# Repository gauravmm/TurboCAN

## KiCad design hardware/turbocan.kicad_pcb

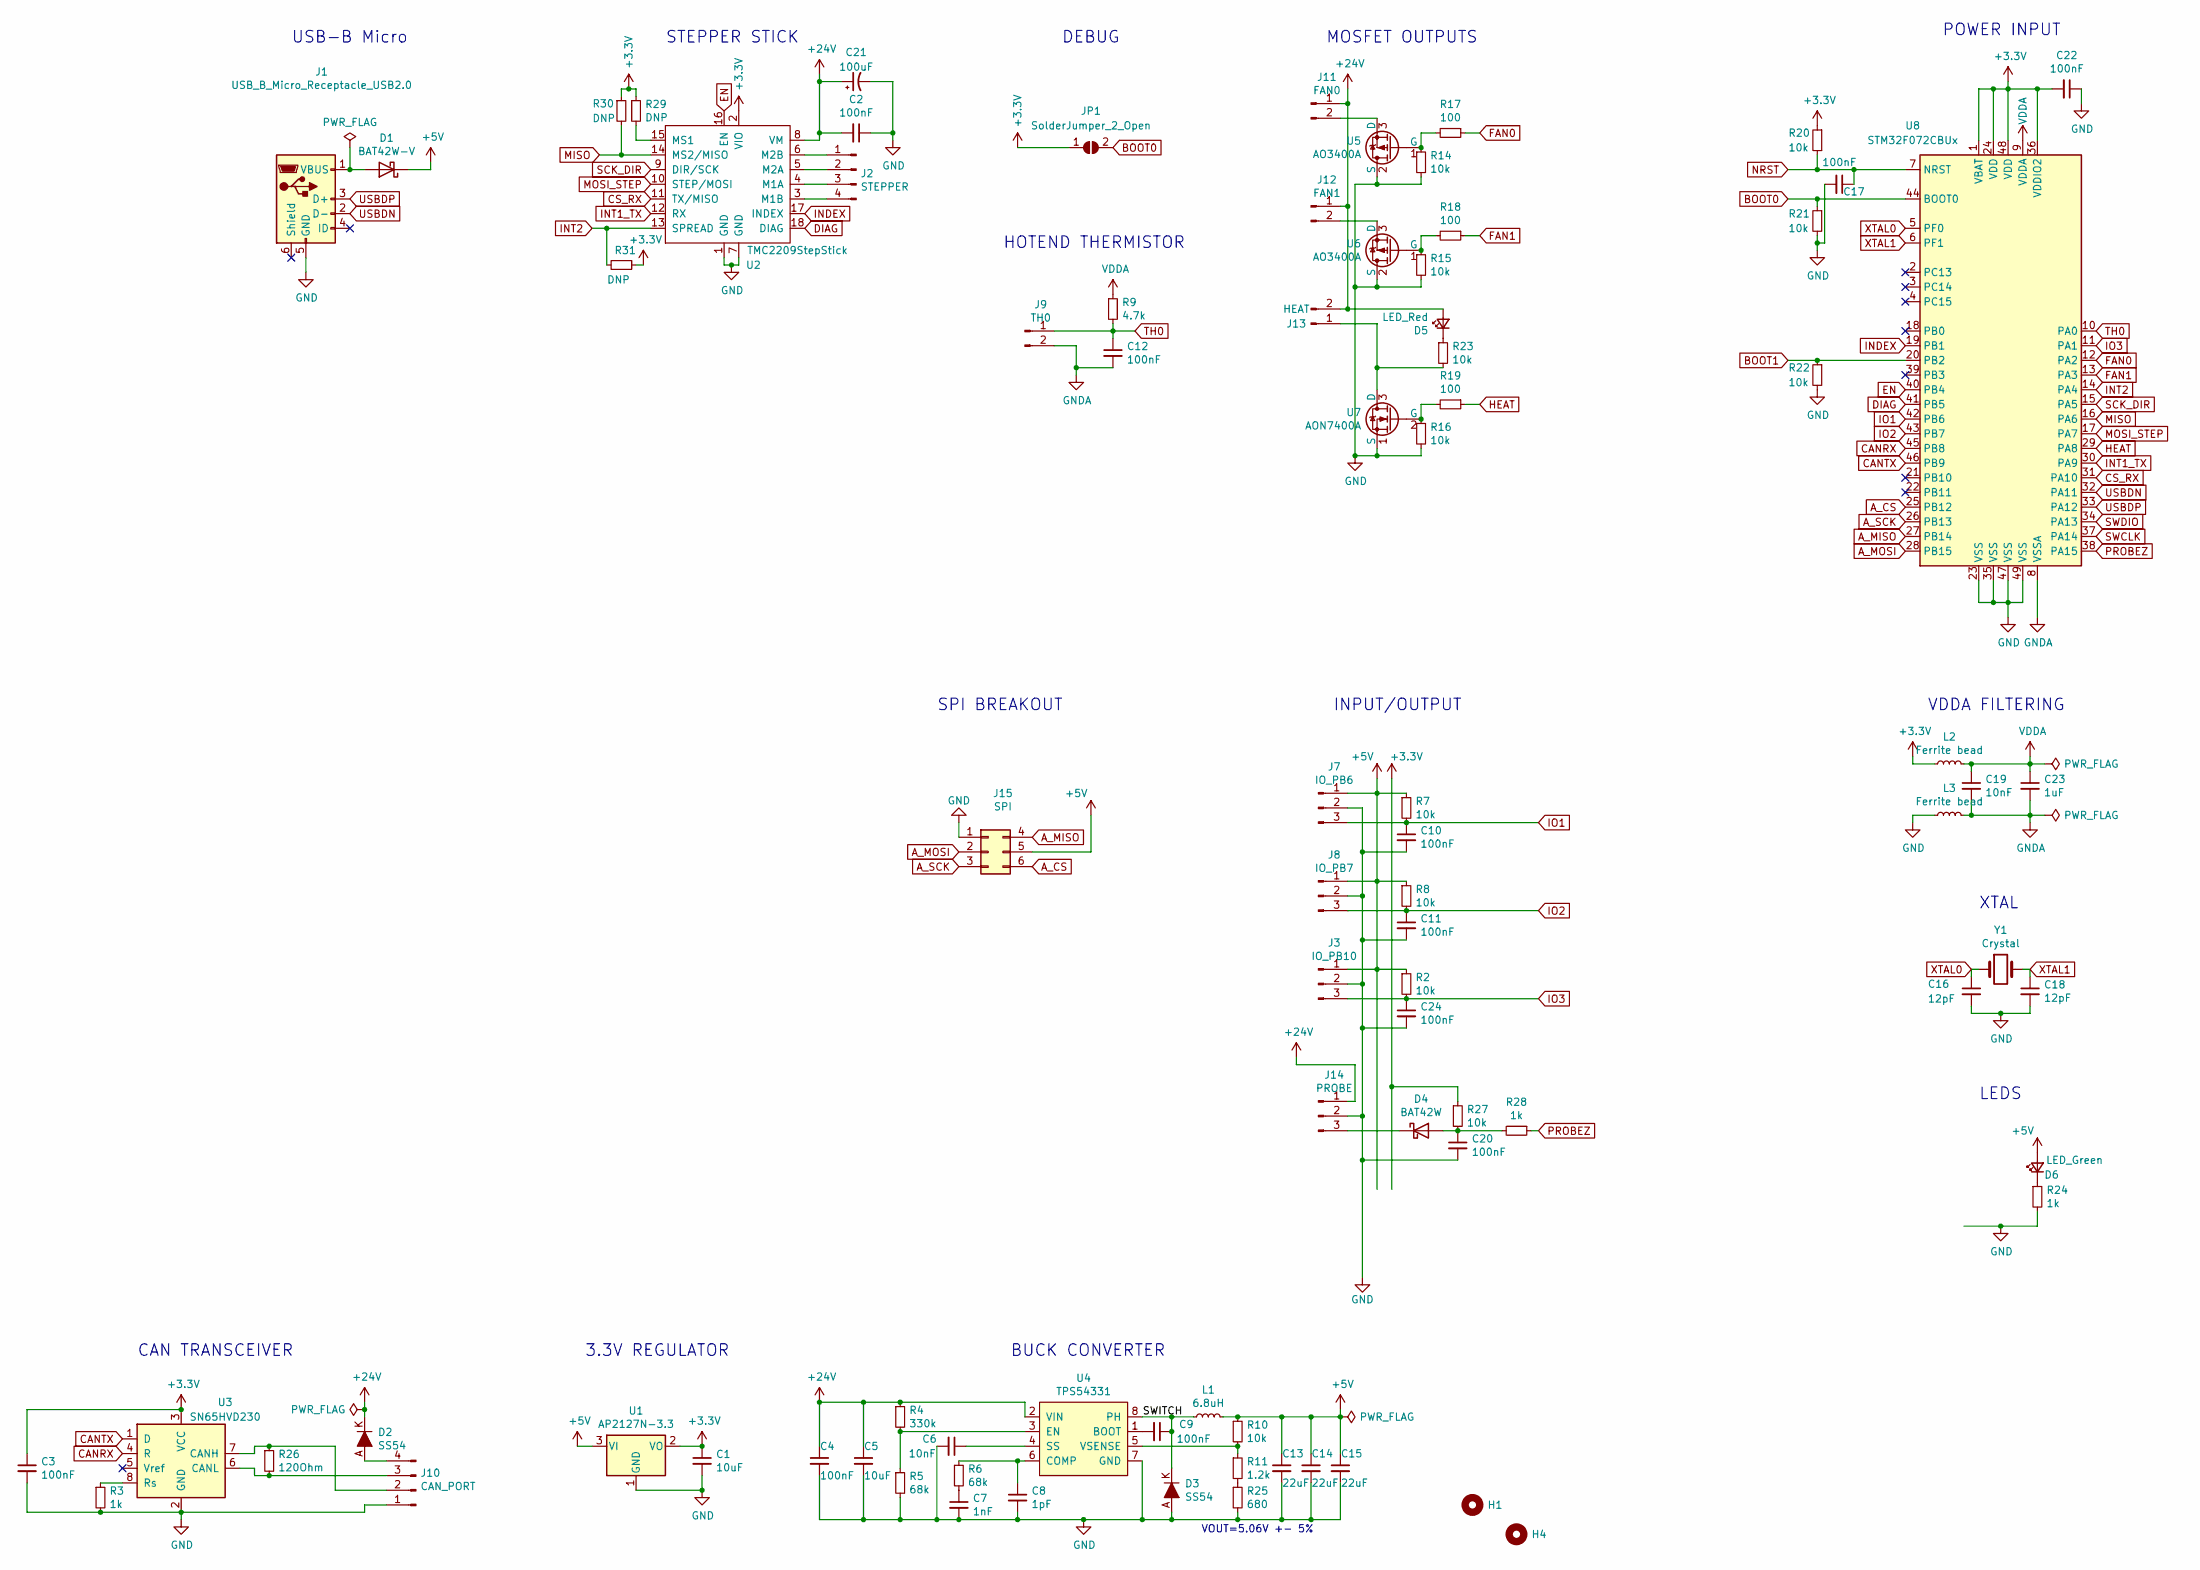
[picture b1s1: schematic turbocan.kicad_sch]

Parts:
C1, C5: 10uF; C_0805_2012Metric; LCSC Part Number C15850
C2, C3, C4, C9, C10, C11, C12, C17, C20, C22, C24: 100nF; C_0402_1005Metric; LCSC Part Number C1525
C6, C19: 10nF; C_0402_1005Metric; LCSC Part Number C15195
C7: 1nF; C_0402_1005Metric; LCSC Part Number C1523
C8: 1pF; C_0402_1005Metric; LCSC Part Number C1550
C13, C14, C15: 22uF; C_0805_2012Metric; LCSC Part Number C45783
C16, C18: 12pF; C_0402_1005Metric; LCSC Part Number C1547
C21: 100uF; CP_Elec_8x10; LCSC Part Number C59944
C23: 1uF; C_0402_1005Metric; LCSC Part Number C52923
D1: BAT42W-V; D_SOD-123; LCSC Part Number C8598
D2, D3: SS54; DO-214AC; MPN SS14; Digi-Key_PN SS14CT-ND
D4: BAT42W; D_SOD-123; LCSC Part Number C8598
D5: LED_Red; LED_0603_1608Metric; LCSC Part Number C2286
D6: LED_Green; LED_0603_1608Metric; LCSC Part Number C72043
H1, H4: MountingHole; MountingHole_3.2mm_M3_DIN965_Pad
J1: USB_B_Micro_Receptacle_USB2.0; USB_Micro-B_Amphenol_10118194_Horizontal
J2: STEPPER; JST_XH_B4B-XH-A_1x04_P2.50mm_Vertical
J3: IO_PB10; JST_XH_B3B-XH-A_1x03_P2.50mm_Vertical
J7: IO_PB6; JST_XH_B3B-XH-A_1x03_P2.50mm_Vertical
J8: IO_PB7; JST_XH_B3B-XH-A_1x03_P2.50mm_Vertical
J9: TH0; JST_XH_B2B-XH-A_1x02_P2.50mm_Vertical
J10: CAN_PORT; JST_XH_B4B-XH-A_1x04_P2.50mm_Vertical
J11: FAN0; JST_XH_B2B-XH-A_1x02_P2.50mm_Vertical
J12: FAN1; JST_XH_B2B-XH-A_1x02_P2.50mm_Vertical
J13: HEAT; JST_XH_B2B-XH-A_1x02_P2.50mm_Vertical
J14: PROBE; JST_XH_B3B-XH-A_1x03_P2.50mm_Vertical
J15: SPI; PinHeader_2x03_P2.54mm_Vertical
JP1: SolderJumper_2_Open; SolderJumper-2_P1.3mm_Open_TrianglePad1.0x1.5mm
L1: 6.8uH; L_SMD_7.3x6.8; LCSC Part Number C207841
L2: Ferrite bead; L_0805_2012Metric; LCSC Part Number C1017
L3: Ferrite bead; L_0805_2012Metric
R2, R7, R8, R10, R14, R15, R16, R20, R21, R22, R27: 10k; R_0402_1005Metric; LCSC Part Number C25744
R3, R24, R28: 1k; R_0402_1005Metric; LCSC Part Number C11702
R4: 330k; R_0402_1005Metric; LCSC Part Number C25778
R5, R6: 68k; R_0402_1005Metric; LCSC Part Number C36871
R9: 4.7k; R_0805_2012Metric; LCSC Part Number C17673
R11: 1.2k; R_0402_1005Metric; LCSC Part Number C25862
R17, R18, R19: 100; R_0402_1005Metric; LCSC Part Number C25076
R23: 10k; R_0402_1005Metric; LCSC Part Number C11702
R25: 680; R_0402_1005Metric; LCSC Part Number C25130
R26: 120Ohm; R_0805_2012Metric; LCSC Part Number C17437
R29, R30, R31: DNP; R_0402_1005Metric
U1: AP2127N-3.3; SOT-23; LCSC Part Number C5446
U2: TMC2209StepStick
U3: SN65HVD230; SOIC-8_3.9x4.9mm_P1.27mm; LCSC Part Number C12084
U4: TPS54331; SOIC-8_3.9x4.9mm_P1.27mm; LCSC Part Number C9865
U5, U6: AO3400A; SOT-23; LCSC Part Number C344010
U7: AON7400A; DFN-8-1EP_3x3mm_P0.65mm_EP1.7x2.05mm_Thermal_Pad; LCSC C85734
U8: STM32F072CBUx; QFN-48-1EP_7x7mm_P0.5mm_EP5.6x5.6mm; LCSC Part Number C92504
Y1: Crystal; Crystal_SMD_5032-2Pin_5.0x3.2mm; LCSC Part Number C115962

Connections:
+3V3: C1.1, C3.1, C22.2, JP1.1 (A), L2.1, R20.1, R27.1, R29.1, R30.1, R31.1, U1.2 (VO), U2.2 (VIO), U3.3 (VCC), U8.1 (VBAT), U8.24 (VDD), U8.36 (VDDIO2), U8.48 (VDD)
+5V: C13.1, C14.1, C15.1, D1.1 (K), D6.2 (A), J3.1, J7.1, J8.1, J15.5, L1.2, R2.1, R7.1, R8.1, R10.1, U1.3 (VI)
+24V: C2.2, C4.1, C5.1, C21.1, D2.K, D5.2 (A), J11.1, J12.1, J13.2, J14.1, R4.1, U2.8 (VM), U4.2 (VIN)
/SWITCH: C9.1, D3.K, L1.1, U4.8 (PH)
A_CS: J15.6, U8.25 (PB12)
A_MISO: J15.4, U8.27 (PB14)
A_MOSI: J15.2, U8.28 (PB15)
A_SCK: J15.3, U8.26 (PB13)
BOOT0: JP1.2 (B), R21.1, U8.44 (BOOT0)
BOOT1: R22.1, U8.20 (PB2)
CANRX: U3.4 (R), U8.45 (PB8)
CANTX: U3.1 (D), U8.46 (PB9)
CS_RX: U2.11 (TX/MISO), U8.31 (PA10)
DIAG: U2.18 (DIAG), U8.41 (PB5)
EN: U2.16 (EN), U8.40 (PB4)
FAN0: R17.1, U8.12 (PA2)
FAN1: R18.1, U8.13 (PA3)
GND: C1.2, C2.1, C3.2, C4.2, C5.2, C6.2, C7.2, C8.2, C10.2, C11.2, C13.2, C14.2, C15.2, C16.2, C17.2, C18.2, C20.2, C21.2, C22.1, C24.2, D3.A, J1.5 (GND), J3.2, J7.2, J8.2, J10.1, J14.2, J15.1, L3.1, R3.2, R5.2, R14.2, R15.2, R16.2, R21.2, R22.2, R24.2, R25.2, U1.1 (GND), U2.1 (GND), U2.7 (GND), U3.2 (GND), U4.7 (GND), U5.2 (S), U6.2 (S), U7.1 (S), U8.23 (VSS), U8.35 (VSS), U8.47 (VSS), U8.49 (VSS)
GNDA: C12.2, C19.2, C23.2, J9.2, L3.2, U8.8 (VSSA)
HEAT: R19.1, U8.29 (PA8)
INDEX: U2.17 (INDEX), U8.19 (PB1)
INT1_TX: U2.12 (RX), U8.30 (PA9)
INT2: R31.2, U2.13 (SPREAD), U8.14 (PA4)
IO1: C10.1, J7.3, R7.2, U8.42 (PB6)
IO2: C11.1, J8.3, R8.2, U8.43 (PB7)
IO3: C24.1, J3.3, R2.2, U8.11 (PA1)
MISO: R30.2, U2.14 (MS2/MISO), U8.16 (PA6)
MOSI_STEP: U2.10 (STEP/MOSI), U8.17 (PA7)
NRST: C17.1, R20.2, U8.7 (NRST)
unnamed: C6.1, U4.4 (SS)
unnamed: C7.1, R6.2
unnamed: C8.1, R6.1, U4.6 (COMP)
unnamed: C9.2, U4.1 (BOOT)
unnamed: C20.1, D4.2 (A), R27.2, R28.2
unnamed: D1.2 (A), J1.1 (VBUS)
unnamed: D2.A, J10.4
unnamed: D4.1 (K), J14.3
unnamed: D6.1 (K), R24.1
unnamed: J2.1, U2.6 (M2B)
unnamed: J2.2, U2.5 (M2A)
unnamed: J2.3, U2.4 (M1A)
unnamed: J2.4, U2.3 (M1B)
unnamed: J10.2, R26.1, U3.7 (CANH)
unnamed: J10.3, R26.2, U3.6 (CANL)
unnamed: J11.2, U5.3 (D)
unnamed: J12.2, U6.3 (D)
unnamed: R3.1, U3.8 (Rs)
unnamed: R4.2, R5.1, U4.3 (EN)
unnamed: R10.2, R11.1, U4.5 (VSENSE)
unnamed: R11.2, R25.1
unnamed: R14.1, R17.2, U5.1 (G)
unnamed: R15.1, R18.2, U6.1 (G)
unnamed: R16.1, R19.2, U7.2 (G)
unnamed: D5.1 (K), R23.1
unnamed: R29.2, U2.15 (MS1)
unnamed: J13.1, R23.2, U7.3 (D)
PROBEZ: R28.1, U8.38 (PA15)
SCK_DIR: U2.9 (DIR/SCK), U8.15 (PA5)
SWCLK: U8.37 (PA14)
SWDIO: U8.34 (PA13)
TH0: C12.1, J9.1, R9.2, U8.10 (PA0)
USBDN: J1.2 (D-), U8.32 (PA11)
USBDP: J1.3 (D+), U8.33 (PA12)
VDDA: C19.1, C23.1, L2.2, R9.1, U8.9 (VDDA)
XTAL0: C16.1, U8.5 (PF0), Y1.1
XTAL1: C18.1, U8.6 (PF1), Y1.2

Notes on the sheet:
VDDA FILTERING
LEDS
HOTEND THERMISTOR
CAN TRANSCEIVER
STEPPER STICK
BUCK CONVERTER
MOSFET OUTPUTS
INPUT/OUTPUT
VOUT=5.06V +- 5%
3.3V REGULATOR
XTAL
SPI BREAKOUT
USB-B Micro
DEBUG
POWER INPUT

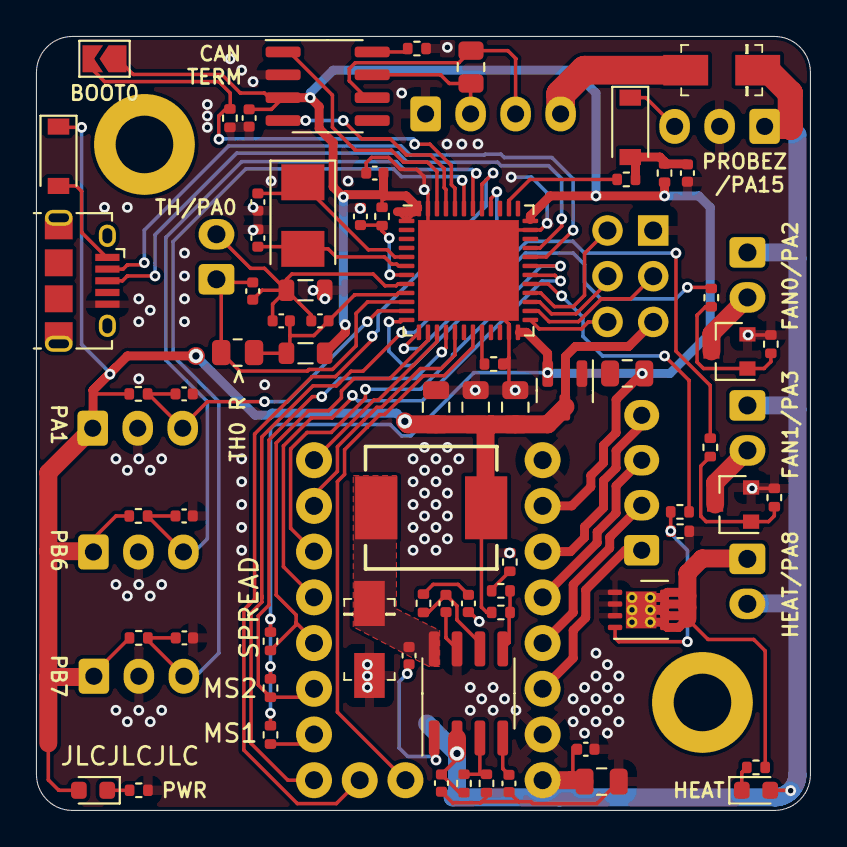
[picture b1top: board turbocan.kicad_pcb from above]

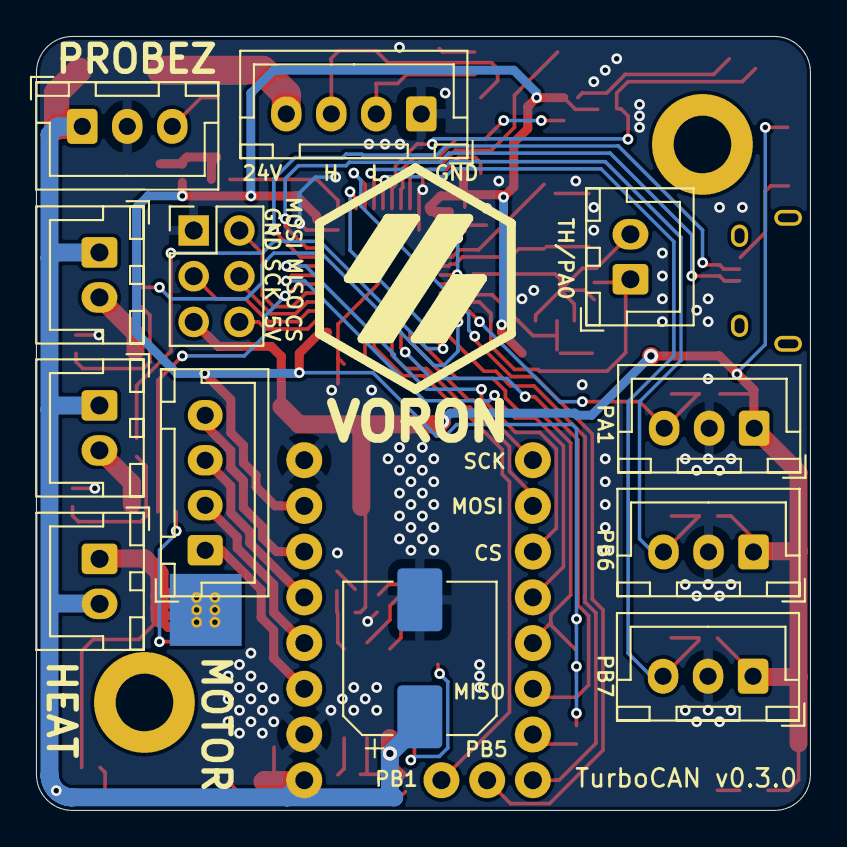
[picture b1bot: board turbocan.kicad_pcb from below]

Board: 2 copper layers, 43.0 x 43.0 mm, 85 parts (13 on the bottom side), 64 nets.

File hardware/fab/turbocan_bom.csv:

Comment,Designator,Footprint,LCSC Part #
10uF ,"C1,C5",C_0805_2012Metric,C15850
100nF ,"C2,C3,C4,C9,C10,C11,C12,C17,C20,C22,C24",C_0402_1005Metric,C1525
10nF ,"C6,C19",C_0402_1005Metric,C15195
1nF ,C7,C_0402_1005Metric,C1523
1pF ,C8,C_0402_1005Metric,C1550
22uF ,"C13,C14,C15",C_0805_2012Metric,C45783
12pF ,"C16,C18",C_0402_1005Metric,C1547
100uF ,C21,CP_Elec_8x10,C59944
1uF ,C23,C_0402_1005Metric,C52923
BAT42W-V ,D1,D_SOD-123,C8598
SS54 ,"D2,D3",DO-214AC,C22452
BAT42W ,D4,D_SOD-123,C8598
LED_Red ,D5,LED_0603_1608Metric,C2286
LED_Green ,D6,LED_0603_1608Metric,C72043
MountingHole ,"H1,H2,H3,H4",MountingHole_3.2mm_M3_DIN965_Pad,
USB_C_Receptacle_USB2.0 ,J1,USB_C_Receptacle_HRO_TYPE-C-31-M-12,
STEPPER ,J2,JST_XH_B4B-XH-A_1x04_P2.50mm_Vertical,
DEBUG ,J5,PinHeader_2x03_P2.54mm_Vertical,
ENDSTOPX ,J7,JST_XH_B3B-XH-A_1x03_P2.50mm_Vertical,
ENDSTOPY ,J8,JST_XH_B3B-XH-A_1x03_P2.50mm_Vertical,
TH0 ,J9,JST_XH_B2B-XH-A_1x02_P2.50mm_Vertical,
CAN_PORT ,J10,JST_XH_B4B-XH-A_1x04_P2.50mm_Vertical,
FAN0 ,J11,JST_XH_B2B-XH-A_1x02_P2.50mm_Vertical,
FAN1 ,J12,JST_XH_B2B-XH-A_1x02_P2.50mm_Vertical,
HEAT ,J13,JST_XH_B2B-XH-A_1x02_P2.50mm_Vertical,
PROBE ,J14,JST_XH_B3B-XH-A_1x03_P2.50mm_Vertical,
6.8uH ,L1,L_SMD_7.3x6.8,C207841
Ferrite bead ,"L2,L3",L_0805_2012Metric,C1017
1k ,"R3,R24,R28",R_0402_1005Metric,C11702
330k ,R4,R_0402_1005Metric,C25778
68k ,"R5,R6",R_0402_1005Metric,C36871
10k ,"R2,R7,R8,R10,R14,R15,R16,R20,R21,R22,R23,R27",R_0402_1005Metric,C25744
4.7k ,R9,R_0805_2012Metric,C17673
1.2k ,R11,R_0402_1005Metric,C25862
100 ,"R17,R18,R19",R_0402_1005Metric,C25076
680 ,R25,R_0402_1005Metric,C25130
120Ohm ,R26,R_0805_2012Metric,C17437
DNP ,"R29,R30,R31",R_0402_1005Metric,
AP2127N-3.3 ,U1,SOT-23,C5446
TMC2209StepStick ,U2,TMC2209StepStick,
SN65HVD230 ,U3,SOIC-8_3.9x4.9mm_P1.27mm,C12084
TPS54331 ,U4,SOIC-8_3.9x4.9mm_P1.27mm,C9865
AO3400A ,"U5,U6",SOT-23,C344010
AON7400A ,U7,DFN-8-1EP_3x3mm_P0.65mm_EP1.7x2.05mm,C85734
STM32F072CBUx ,U8,QFN-48-1EP_7x7mm_P0.5mm_EP5.6x5.6mm,C92504
ADXL345BCCZ ,U9,LGA-14_3x5mm_RevA,C9667
Crystal ,Y1,Crystal_SMD_5032-2Pin_5.0x3.2mm,C115962
USBMicro,J1,USB_B_Micro_Receptacle_USB2.0,C132562

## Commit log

2022-03-18 Upgraded to KiCAD 6
2022-03-21 Updated schematic with generic IO, removed ADXL.
2022-03-21 First Test
2022-03-22 Before DRC
2022-03-22 Fixed violations, still have more DRC.
2022-03-23 First Manufacturing Upload
2022-03-23 Updated manufacturer files for 0.3.0 first draft.
2022-03-23 Change headers to be compatible with JLCPCB
2022-03-23 First manufacturing draft.
